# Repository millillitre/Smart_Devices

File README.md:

# Smart Devices

Développé par Marie-Lien Da Costa Bento, Célian Hilal Hamdan et Jean-Phillipe Loubejac--Combalbert pour le cours *Microcontroller and Open Source Hardware*.

## Organisation

Dans ce repo, vous pourrez trouver:

- sur la branche *main*:
  - Les fichiers de schémas et de routage [KiCad](/KiCAD/)
  - Les fichiers de simulation [LTSpice](/LTSpice/)
  - Le montage du [transceiver LoRa](/LoRa) pour notre réseau et sa [configuration arduino](/LoRa/LoRaConnection.ino).
  - Les configurations [MIT_App](/MIT_App/) sur la partie application.
  - Les fichiers de configuration [Node-RED](/NodeRED/)
  - Les différents [documents](/docs/) (photos, screenshots) utilisés pour appuyer notre propos.
  - La licence *Creative Commons*
  - La [datasheet](/Datasheet_gaz_sensor.pdf) de notre capteur.
  - [README.md](/README.md)

## Usage

### Matériels

Pour effectuer le projet, nous avons utilisé:
    - une carte Arduino UNO, 
    - un module LoRa,
    - les capteurs de gaz conçues à l'AIME.

### Communication

Pour obtenir les données via LoRa, nous avons eu besoin d'un accès à une gateway LoRa and un serveur (Chirpstack de l'INSA Toulouse dans notre cas)

## Le capteur de GAZ effectué à l'AIME

Voici, étape par étape, le travail que nous avons effectué pour fabriquer notre capteur à l'AIME.

### Etape 1 : Fabrication des nanoparticules du capteur

1. Synthèse des nanoparticules : préparation de nanobâtonnets de WO₃

   - Préparation des précurseurs (Na₂WO₄·2H₂O et NaCl)
   - Préparation de l’acide (HCl)
   - Recuit et refroidissement

2. Traitement post-synthèse des nanoparticules

   - Centrifugation
   - Stockage des nanobâtonnets dans un flacon

### Etape 2: Fabrication de la puce du capteur

1. Procédé de fabrication de la puce : [photolithographie métallique](/docs/Mask.jpg)

   - Séchage et dépôt de résine photosensible
   - Exposition aux UV
   - Développement
   - Gravure de l’aluminium
   - Recuit du métal
   - Sélection des meilleures puces

2. Conditionnement et assemblage du dispositif

   - Découpe diamantée de la puce
   - Montage sur le support à l’aide d’un adhésif époxy et polymérisation
   - Soudage par ultrasons des fils aluminium-silicium pour les connexions électriques

### Etape 3 : Fabrication de la phase finale du capteur

1. Procédé de diélectrophorèse

   - Intégration des nanoparticules (NP) par diélectrophorèse
   - Application d’une tension sinusoïdale aux électrodes interdigitées Peigne d'électrodes
   - Positionnement précis des nanoparticules sur le dispositif

### Etape 4 : Tests du capteur

1. Tests électriques préliminaires

   - Mesure des résistances aux bornes du capteur
   - Vérification des connexions électriques et du fonctionnement

2. Tests fonctionnels sous atmosphère gazeuse

   - Tests sous méthane, air synthétique et éthanol à 250 °C (522 K)

### Etape 5 : Caractérisation du capteur

1. Analyse par microscopie électronique à balayage (MEB)

   - Observation du capteur et de ses nanobâtonnets par [MEB](/docs/MEB.tif)

## Amplification du signal

Lors des TP d'Analog Electronic Labs, on a modélisé sur LTSpice un amplificateur. On peut le tretrouver [ici](/LTSpice/ampliyoplait_avec_capteur.asc).

Nous avons également mis en place l'amplificateur en banc de test [ici](/docs/montage_ampliop.png).

## Programmation du capteur et transmission via LoRa

### Montage et soudure du banc de test

Nous avons soudé et monté un transceiver LoRa pour notre réseau. Les détails de ces étapes sont accessibles [ici](/LoRa/README.md).

Nous avons également testé électriquement avec un wattmètre notre soudure.

### Transmission LoRa

Les communications sont accessibles sur [https://srv-chirpstack.insa-toulouse.fr](chirpstack).

## Conception du PCB via KiCAD
Nous avons suivi les instructions de M.Biganzoli, et nous avons décidé de faire une seule face, pour ne pas avoir de via et éviter d'avoir à connecter par nous me^me l'autre côté à l'aide de fils. 

Les fichiers du PCB sont trouvables [ici](/KiCAD/kicad-roger-shield-uno/).

Nous avons pu ensuite l'imprimer avec Cathy et nous avons percé un à un les trous. Nous avons également souder par la suite. Ci-dessous notre PCB imprimé et le montage:

## Node-RED

Nous avons développé un tableau de bord avec [Node-RED](/NodeRED/flows.json) pour visualiser les données transmises via LoRa. Ce tableau de bord simple affiche :
    - la dernière valeur mesurée,
    - une jauge indiquant la position de cette valeur par rapport aux seuils minimum et maximum de gaz détectables par le capteur,
    - ainsi que la variation de la quantité de gaz.

Ensuite nous avons continué notre développement ([flows2.json](/NodeRED/flows2.json)) en ajoutant une partie pour créer un fichier json pour envoyer en http la valeur du capteur pour permettre à celle-ci d'être récupérée par l'application mentionnée dans la partie suivante.

## MIT Application
Nous avons mis en place une application pour mobile via MIT App, elle se trouve [ici](/MIT_App/Application/). L'idée de cette application est d'afficher la valeur du capteur de gaz en temps réel, qui change de coucleur si la valeur est critique et qui affiche un graphe d'évolution des valeurs.

- Valeur sous le seuil critique :

- Valeur au dessus du seuil critique :

- Visualisation graphique :

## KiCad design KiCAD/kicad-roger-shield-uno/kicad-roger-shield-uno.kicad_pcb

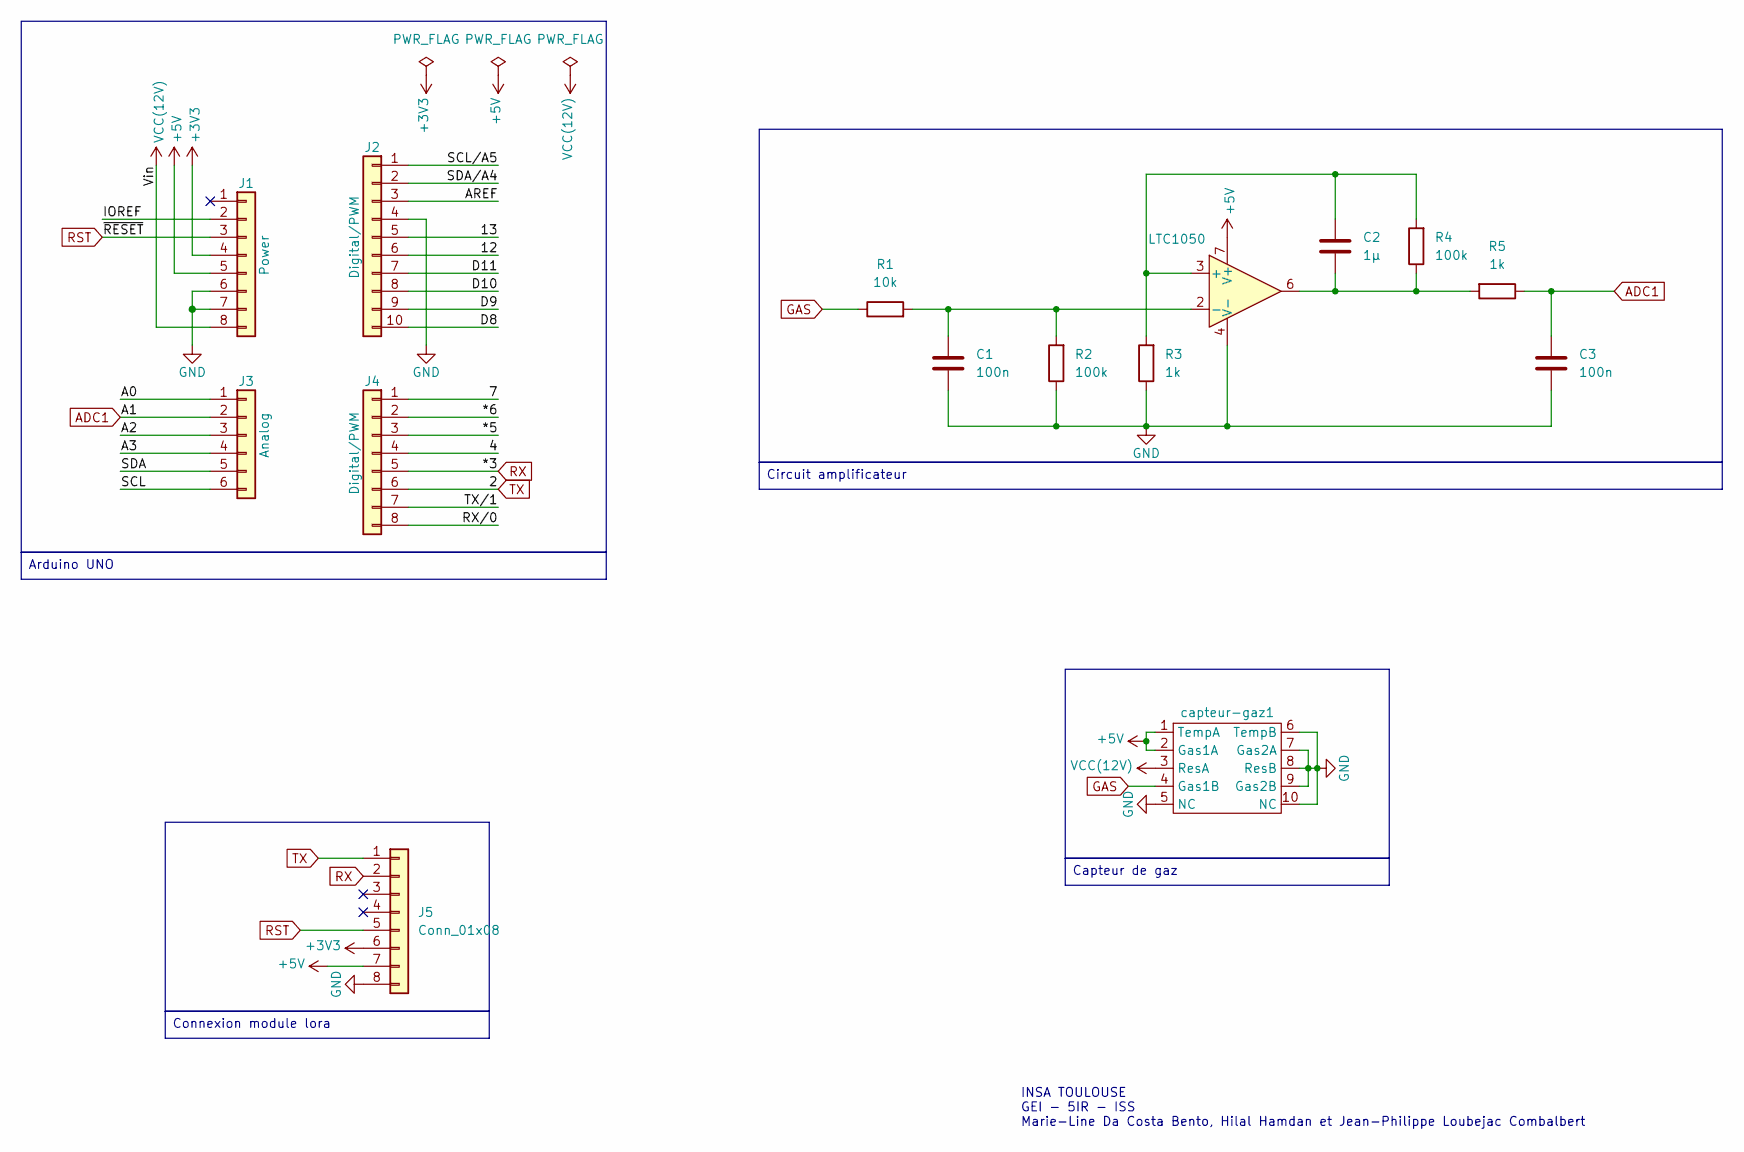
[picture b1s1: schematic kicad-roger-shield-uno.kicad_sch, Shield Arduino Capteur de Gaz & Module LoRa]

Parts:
C1, C3: 100n; C_Disc_D7.0mm_W2.5mm_P5.00mm
C2: 1µ; C_Disc_D7.0mm_W2.5mm_P5.00mm
J1: Power; PinHeader_1x08_P2.54mm_Vertical
J2: Digital/PWM; PinHeader_1x10_P2.54mm_Vertical
J3: Analog; PinHeader_1x06_P2.54mm_Vertical
J4: Digital/PWM; PinHeader_1x08_P2.54mm_Vertical
J5: Conn_01x08; PinSocket_1x08_P2.54mm_Vertical
R1: 10k; R_Axial_DIN0207_L6.3mm_D2.5mm_P10.16mm_Horizontal
R2, R4: 100k; R_Axial_DIN0207_L6.3mm_D2.5mm_P10.16mm_Horizontal
R3, R5: 1k; R_Axial_DIN0207_L6.3mm_D2.5mm_P10.16mm_Horizontal
U2: LTC1050; DIP-8_W7.62mm
capteur-gaz1: TO-5-10_Window

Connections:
+3V3: J1.4, J5.6
+5V: J1.5, J5.7, U2.7 (V+), capteur-gaz1.1 (TempA), capteur-gaz1.2 (Gas1A); also elsewhere on the board
/4: J4.4
/7: J4.1
/12: J2.6
/13: J2.5
/*5: J4.3
/*6: J4.2
/A0: J3.1
/A2: J3.3
/A3: J3.4
/AREF: J2.3
/D8: J2.10
/D9: J2.9
/D10: J2.8
/D11: J2.7
/IOREF: J1.2
/RX/0: J4.8
/SCL: J3.6
/SCL/A5: J2.1
/SDA: J3.5
/SDA/A4: J2.2
/TX/1: J4.7
ADC1: C3.1, J3.2, R5.1
GAS: R1.1, capteur-gaz1.4 (Gas1B); also elsewhere on the board
GND: C1.2, C3.2, J1.6, J1.7, J2.4, J5.8, R2.1, R3.1, U2.4 (V-), capteur-gaz1.5 (NC), capteur-gaz1.6 (TempB), capteur-gaz1.7 (Gas2A), capteur-gaz1.8 (ResB), capteur-gaz1.9 (Gas2B), capteur-gaz1.10 (NC); also elsewhere on the board
unnamed: C2.2, R4.1, R5.2, U2.6
unnamed: C2.1, R3.2, R4.2, U2.3 (+)
unnamed: C1.1, R1.2, R2.2, U2.2 (-)
RST: J1.3, J5.5
RX: J4.5, J5.2
TX: J4.6, J5.1
VCC(12V): J1.8, capteur-gaz1.3 (ResA); also elsewhere on the board

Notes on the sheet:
INSA TOULOUSE GEI - 5IR - ISS Marie-Line Da Costa Bento, Hilal Hamdan et Jean-Philippe Loubejac Combalbert
Circuit amplificateur
Arduino UNO
Capteur de gaz
Connexion module lora

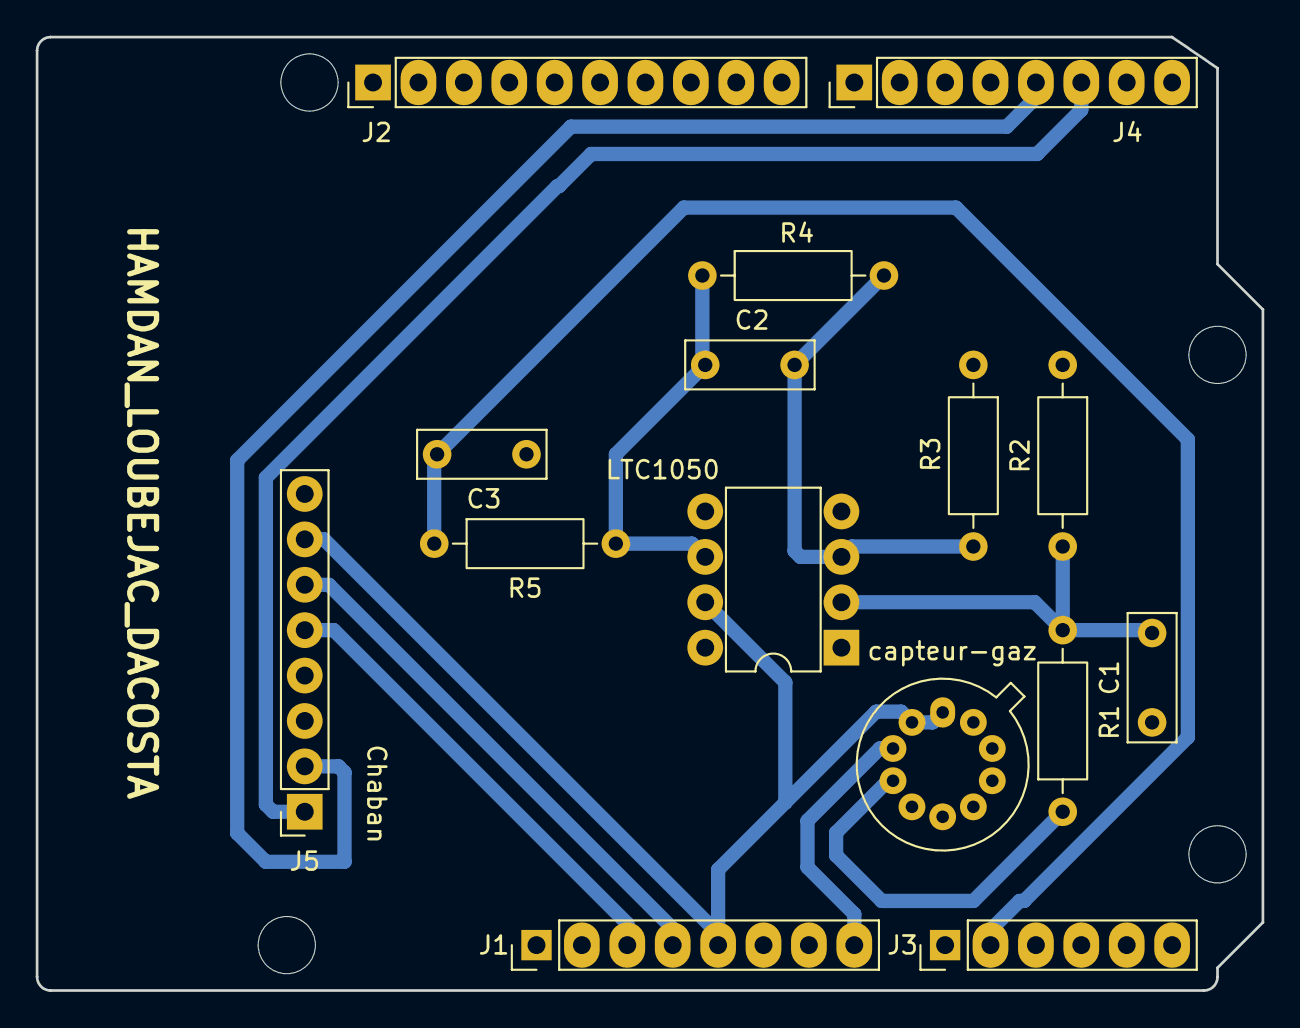
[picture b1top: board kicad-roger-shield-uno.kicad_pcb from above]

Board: 2 copper layers, 68.6 x 53.3 mm, 19 parts (0 on the bottom side), 12 nets.

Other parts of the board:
MH1, MH2, MH3, MH4: MountingHole_3.2mm
capteur-gaz: TO-5-10_Window

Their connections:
+5V: capteur-gaz.1 (TempA), capteur-gaz.2 (Gas1A); also elsewhere on the board
GAS: capteur-gaz.4 (Gas1B); also elsewhere on the board
GND: capteur-gaz.5 (NC), capteur-gaz.6 (TempB), capteur-gaz.7 (Gas2A), capteur-gaz.8 (ResB), capteur-gaz.9 (Gas2B), capteur-gaz.10 (NC); also elsewhere on the board
VCC(12V): capteur-gaz.3 (ResA); also elsewhere on the board

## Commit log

2025-12-08 Adding TP1
2025-12-08 Deleting files
2025-12-08 Fix formatting of project name in README
2025-12-08 Fix formatting of UART communication bus list
2025-12-12 Adding some docs and a structure
2025-12-12 Adding readmes
2025-12-12 add: ltspice circuit
2025-12-12 add: une superbe image du circuit
2025-12-12 feature: adding some files
    - README: adding some README files
    - LoRa connection file
2025-12-12 refactor(feature): updating LoRa transceiver code
2025-12-17 Add AppEUI and AppKey values for OTAA join
    Populated the Eui and Key variables with actual AppEUI and AppKey values required for joining Chirpstack via OTAA.
2025-12-17 Add LoRa connection image and update documentation
    - Added a new image showing the LoRa transceiver connection to Arduino in docs/LoRa_connection.jpg.
2025-12-17 Add LoRa LED example and update documentation
2025-12-17 add photo montage ampliop
2026-01-05 Add MIT App project files and documentation
    Added initial files for the MIT App project, including application source (.aia), block and screen images, and a README describing the app and its connection to Arduino.
2026-01-05 Add fabrication steps and images to documentation
    Expanded the README.md with detailed step-by-step instructions for sensor fabrication, including nanoparticle synthesis, chip manufacturing, assembly, testing, and characterization. Added references 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
2026-01-05 Enable LoRa data transmission and update documentation
    Uncommented the LoRa data transmission and delay in LoRaConnectionWithLED.ino to send sensor values every 10 seconds. Updated LoRa/README.md and main README.md with additional documentation and added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
2026-01-05 Remove Arduino code references and README
    Deleted the Arduino/README.md file and removed references to Arduino code from the main README.md.
2026-01-06 Add initial Node-RED flow configuration
2026-01-06 Add gauge photo
2026-01-06 fix center image
2026-01-06 Add package.json with dependencies for Node-RED
2026-01-06 Refactor MIT_App structure and update documentation
2026-01-06 Add gas sensor datasheet and update README
    Added Datasheet_gaz_sensor.pdf to the repository.
2026-01-08 add: gitignore to ignore kicad backups file
2026-01-08 add: kicad roger project
2026-01-09 Updating the datasheet
2026-01-09 Updating datasheet file
2026-01-09 Update README with project results and PCB details
2026-01-09 Update Node-RED dashboard and development details in README
2026-01-09 Uploading screen of KiCAD
2026-01-09 add applications screenshots
2026-01-09 Update README with images for gas sensor application
    Added images for critical and non-critical gas sensor values.
2026-01-09 add nodeRED http conf file
2026-01-09 add application code file
2026-01-09 add screenshots of blocks on MIT App
2026-01-09 Update file system
2026-01-09 add screen flows 2
2026-01-10 Updating datasheet
